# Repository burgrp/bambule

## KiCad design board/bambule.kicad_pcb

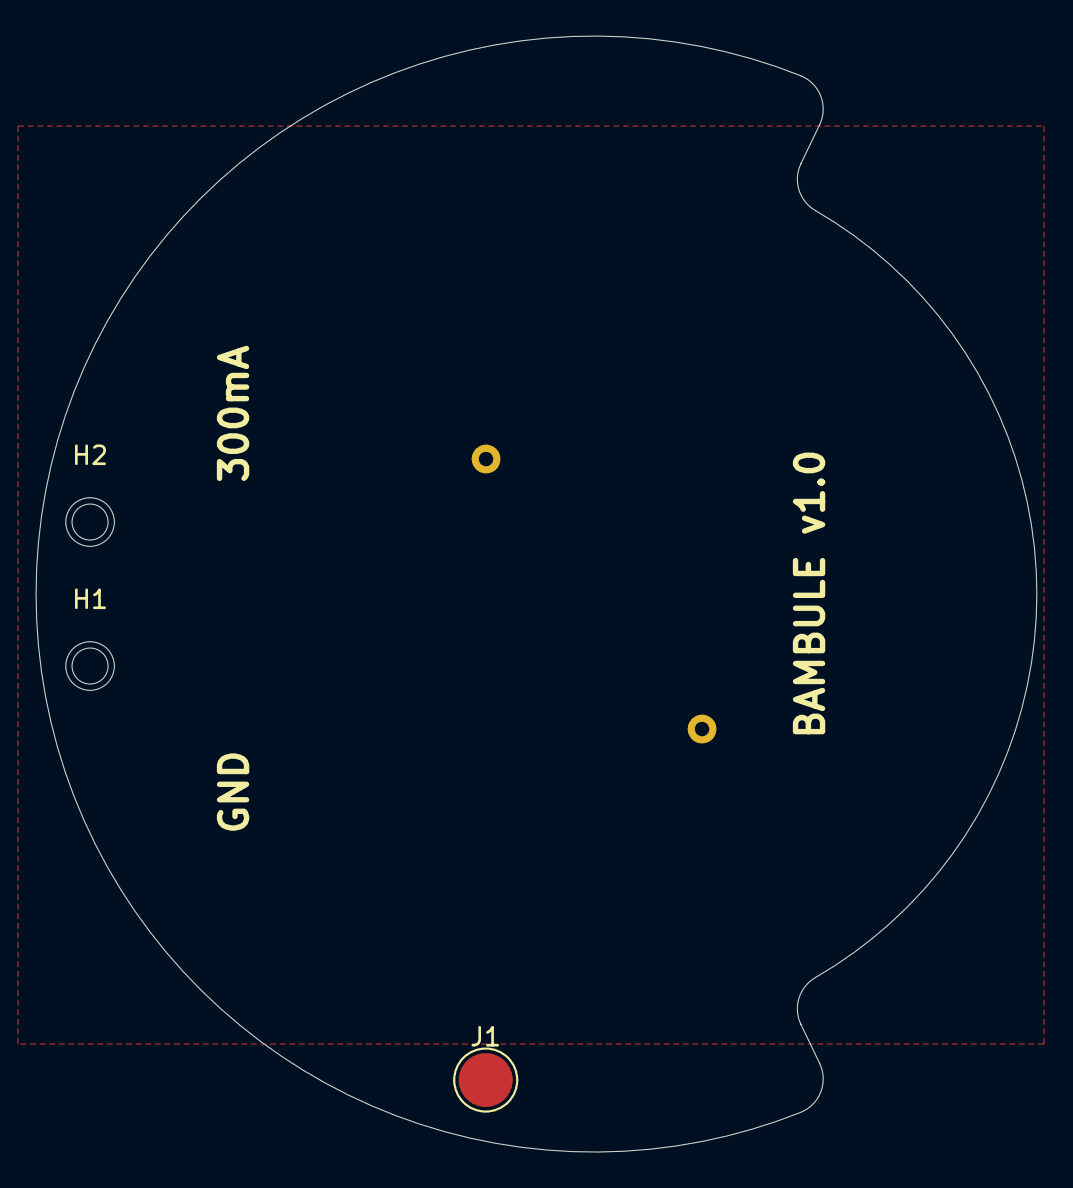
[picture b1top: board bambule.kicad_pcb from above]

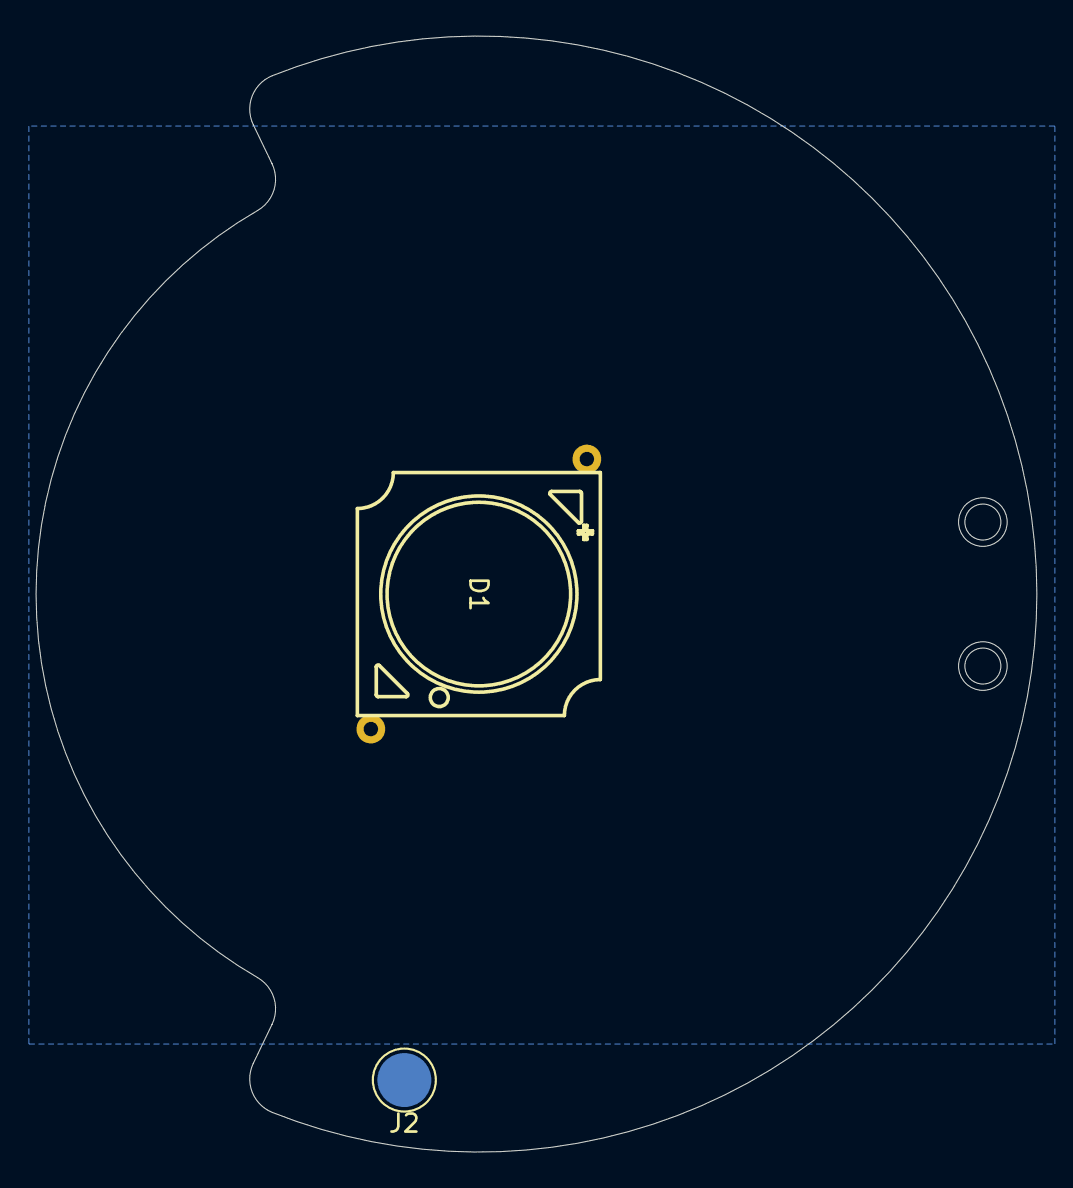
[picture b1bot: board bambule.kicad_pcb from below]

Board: 2 copper layers, 55.6 x 62.0 mm, 5 parts (2 on the bottom side), 3 nets, no tracks yet.

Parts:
D1: LED_Series; LED_BXRE_V10
H1, H2: MountingHole_Pad; MountingHole_2.7mm
J1, J2: Conn_01x01_Female; TestPoint_Pad_D3.0mm

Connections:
/GND: D1.1, J2.1
/HEATSINK: H1.1, H2.1
/VIN: D1.2, J1.1
